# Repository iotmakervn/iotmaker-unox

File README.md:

# IoT Maker - UnoX

## Features

IoTMaker UnoX:  
- Power input 6.5V to 12VDC - recomment 9V (1A/5V output) and 5V USB
- Additional Button, LED, header for external module : variable, servo, common sensor.
- Open hardware with CC-BY-SA license
- Design with KiCad

## Hardware

### Schematics

### PCB Layout

### 3D

### Pinout 

### Gerber

[Download gerber sigle](./assets/iotmaker-arduino-uno-68,58x53,34mm.zip)

[Download gerber panel](./assets/panel-iotmaker-arduino-uno.zip)

### Remark

This project was in development phase - we will remove this remark after release

# License

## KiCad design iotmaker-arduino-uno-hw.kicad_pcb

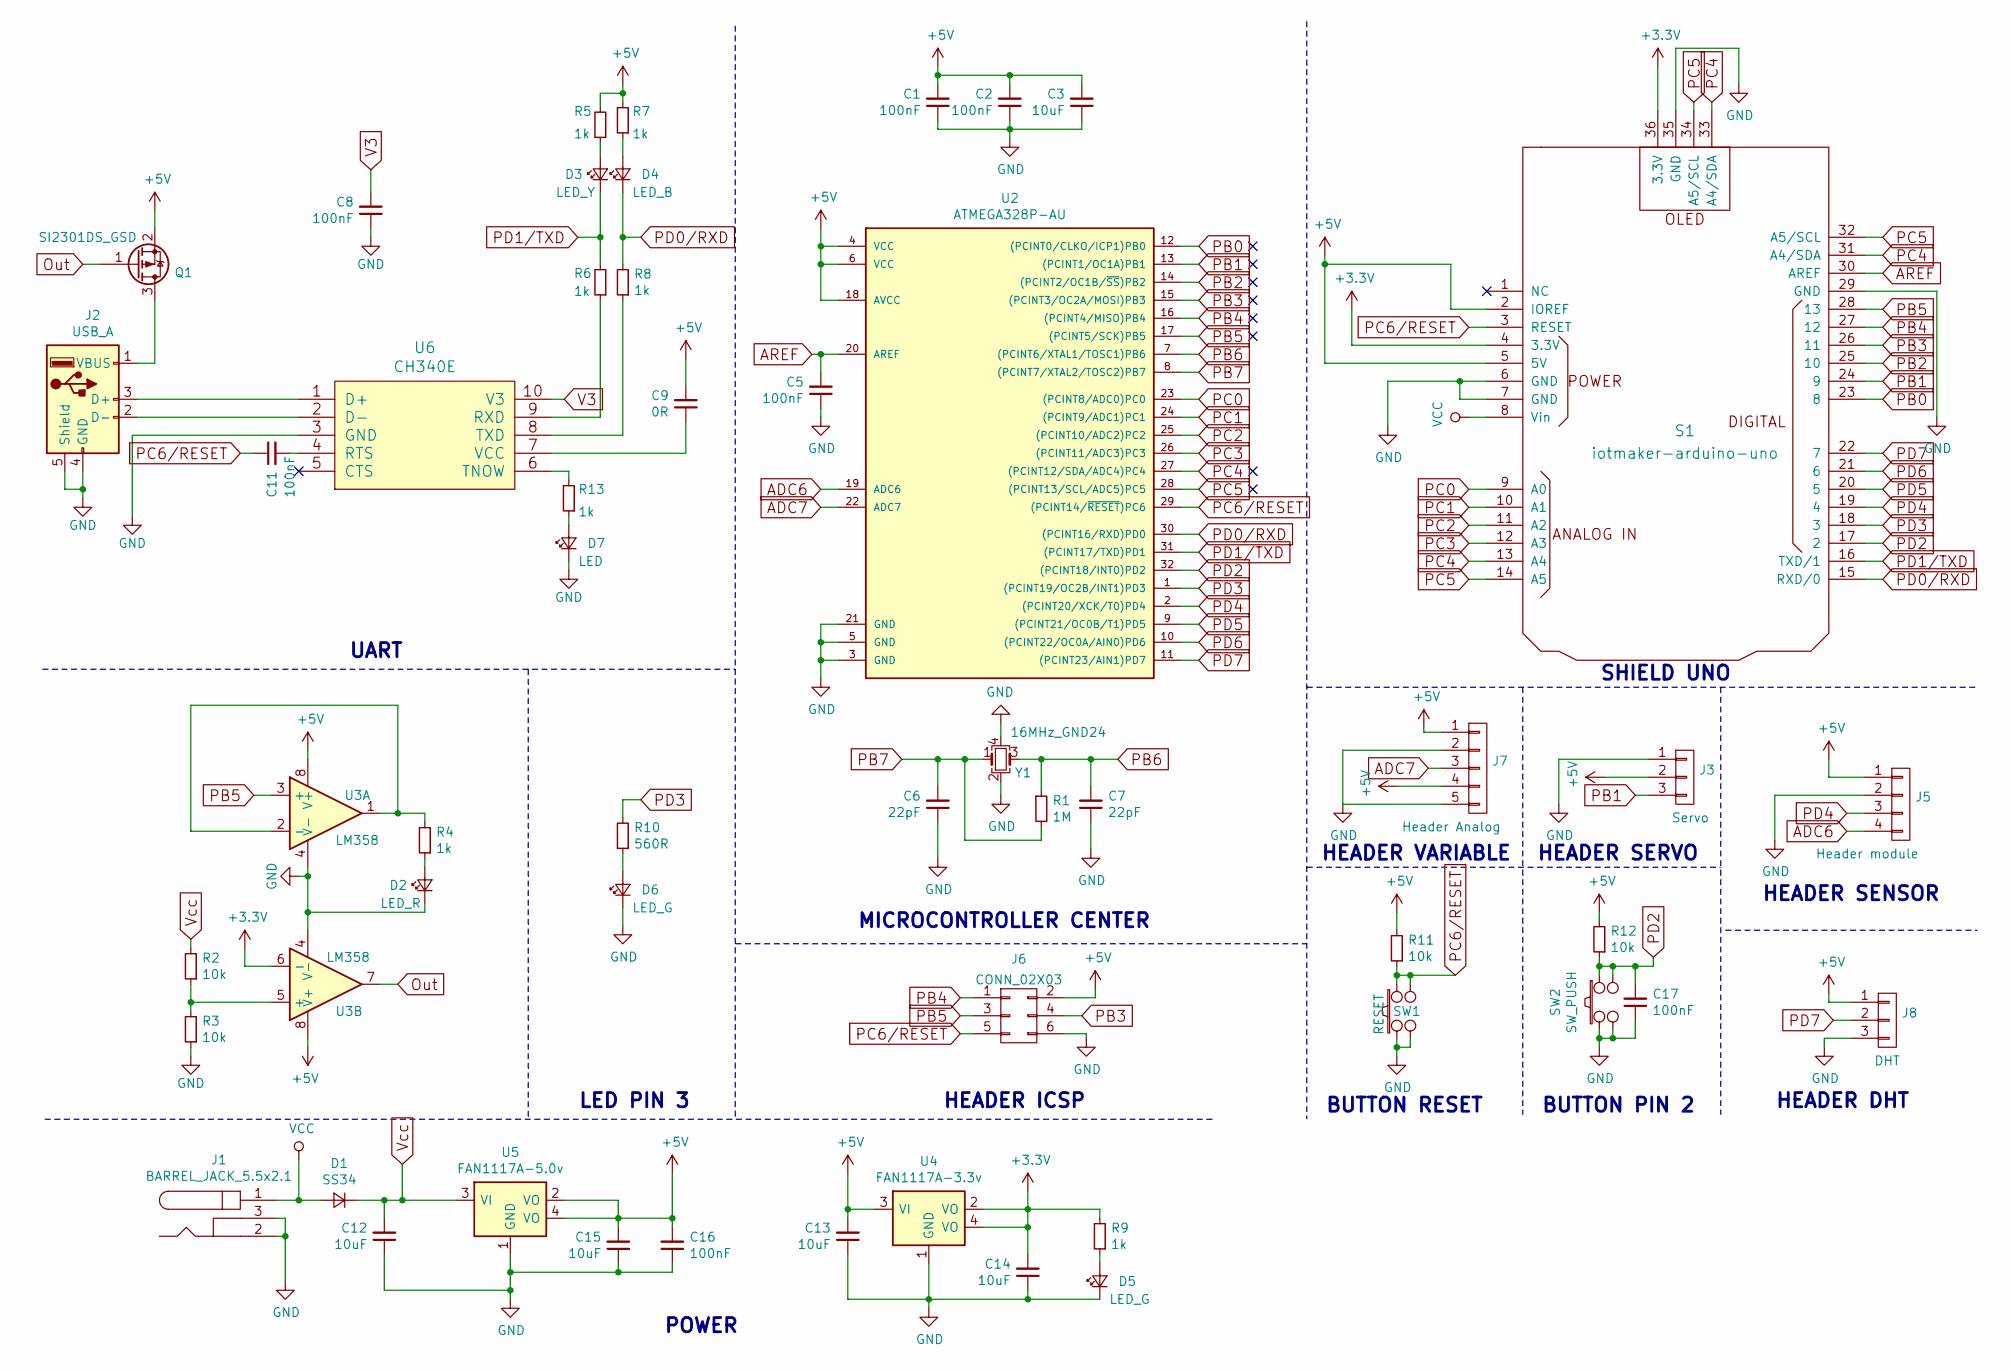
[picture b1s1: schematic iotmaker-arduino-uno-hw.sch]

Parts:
C1, C2, C5, C8, C11, C16, C17: 100nF; C_0603
C3: 10uF; C_0603
C6, C7: 22pF; C_0603
C9: 0R; C_0603
C12, C13, C14, C15: 10uF; C_1210
D1: SS34; D_SMA-SMB_Universal_Handsoldering
D2: LED_R; LED_0603
D3: LED_Y; LED_0603
D4: LED_B; LED_0603
D5, D6: LED_G; LED_0603
D7: LED; LED_0603
J1: BARREL_JACK_5.5x2.1; BARREL_JACK
J2: USB_A; MicroUSB-B
J3: Servo; Pin_Header_Straight_1x03_Pitch2.54mm
J5: Header module; Pin_Header_Straight_1x04_Pitch2.54mm
J6: CONN_02X03; Pin_Header_Straight_2x03_Pitch2.54mm
J7: Header Analog; Pin_Header_Straight_1x05_Pitch2.54mm
J8: DHT; Pin_Header_Straight_1x03_Pitch2.54mm
Q1: SI2301DS_GSD; SOT-23_standar
R1: 1M; R_0603
R2, R3, R11, R12: 10k; R_0603
R4, R5, R6, R7, R8, R9, R13: 1k; R_0603
R10: 560R; R_0603
S1: iotmaker-arduino-uno
SW1: RESET; smd_push2
SW2: SW_PUSH; smd_push2
U2: ATMEGA328P-AU; TQFP-32_7x7mm_Pitch0.8mm
U3: LM358; SOIC-8_3.9x4.9mm_Pitch1.27mm
U4: FAN1117A-3.3v; SOT-223
U5: FAN1117A-5.0v; SOT-223
U6: CH340E; MSOP-10_3x3mm_Pitch0.5mm
Y1: 16MHz_GND24; Crystal_SMD_3225-4pin_3.2x2.5mm

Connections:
+3V3: C14.2, R9.2, S1.4 (3.3V), S1.36 (3.3V), U3.6 (-), U4.2 (VO), U4.4 (VO)
+5V: C1.2, C2.2, C3.2, C9.2, C13.2, C15.2, C16.2, J3.2, J5.1, J6.2, J7.1, J7.4, J8.1, Q1.2 (S), R5.2, R7.2, R11.2, R12.2, S1.2 (IOREF), S1.5 (5V), U2.4 (VCC), U2.6 (VCC), U2.18 (AVCC), U3.8 (V+), U4.3 (VI), U5.2 (VO), U5.4 (VO)
ADC6: J5.4, U2.19 (ADC6)
ADC7: J7.3, U2.22 (ADC7)
AREF: C5.2, S1.30 (AREF), U2.20 (AREF)
GND: C1.1, C2.1, C3.1, C5.1, C6.1, C7.1, C8.1, C12.1, C13.1, C14.1, C15.1, C16.1, C17.1, D2.1 (K), D5.1 (K), D6.1 (K), D7.1 (K), J1.2, J1.3, J2.4 (GND), J2.5 (Shield), J3.1, J5.2, J6.6, J7.2, J7.5, J8.3, R3.1, S1.6 (GND), S1.7 (GND), S1.29 (GND), S1.35 (GND), SW1.1, SW1.2, SW2.3, SW2.4, U2.3 (GND), U2.5 (GND), U2.21 (GND), U3.4 (V-), U4.1 (GND), U5.1 (GND), U6.3 (GND), Y1.2, Y1.4
unnamed: C9.1, U6.7 (VCC)
unnamed: C11.2, U6.4 (RTS)
unnamed: D2.2 (A), R4.1
unnamed: D3.2 (A), R5.1
unnamed: D4.2 (A), R7.1
unnamed: D5.2 (A), R9.1
unnamed: D6.2 (A), R10.1
unnamed: D7.2 (A), R13.1
unnamed: J2.1 (VBUS), Q1.3 (D)
unnamed: J2.2 (D-), U6.2 (D-)
unnamed: J2.3 (D+), U6.1 (D+)
unnamed: R2.1, R3.2, U3.5 (+)
unnamed: R4.2, U3.1, U3.2 (-)
unnamed: R6.1, U6.9 (RXD)
unnamed: R8.1, U6.8 (TXD)
unnamed: R13.2, U6.6 (TNOW)
Out: Q1.1 (G), U3.7
PB0: S1.23 (8), U2.12 ((PCINT0/CLKO/ICP1)PB0)
PB1: J3.3, S1.24 (9), U2.13 ((PCINT1/OC1A)PB1)
PB2: S1.25 (10), U2.14 ((PCINT2/OC1B/~SS~)PB2)
PB3: J6.4, S1.26 (11), U2.15 ((PCINT3/OC2A/MOSI)PB3)
PB4: J6.1, S1.27 (12), U2.16 ((PCINT4/MISO)PB4)
PB5: J6.3, S1.28 (13), U2.17 ((PCINT5/SCK)PB5), U3.3 (+)
PB6: C7.2, R1.1, U2.7 ((PCINT6/XTAL1/TOSC1)PB6), Y1.3
PB7: C6.2, R1.2, U2.8 ((PCINT7/XTAL2/TOSC2)PB7), Y1.1
PC0: S1.9 (A0), U2.23 ((PCINT8/ADC0)PC0)
PC1: S1.10 (A1), U2.24 ((PCINT9/ADC1)PC1)
PC2: S1.11 (A2), U2.25 ((PCINT10/ADC2)PC2)
PC3: S1.12 (A3), U2.26 ((PCINT11/ADC3)PC3)
PC4: S1.13 (A4), S1.31 (A4/SDA), S1.33 (A4/SDA), U2.27 ((PCINT12/SDA/ADC4)PC4)
PC5: S1.14 (A5), S1.32 (A5/SCL), S1.34 (A5/SCL), U2.28 ((PCINT13/SCL/ADC5)PC5)
PC6/RESET: C11.1, J6.5, R11.1, S1.3 (RESET), SW1.3, SW1.4, U2.29 ((PCINT14/~RESET~)PC6)
PD0/RXD: D4.1 (K), R8.2, S1.15 (RXD/0), U2.30 ((PCINT16/RXD)PD0)
PD1/TXD: D3.1 (K), R6.2, S1.16 (TXD/1), U2.31 ((PCINT17/TXD)PD1)
PD2: C17.2, R12.1, S1.17 (2), SW2.1, SW2.2, U2.32 ((PCINT18/INT0)PD2)
PD3: R10.2, S1.18 (3), U2.1 ((PCINT19/OC2B/INT1)PD3)
PD4: J5.3, S1.19 (4), U2.2 ((PCINT20/XCK/T0)PD4)
PD5: S1.20 (5), U2.9 ((PCINT21/OC0B/T1)PD5)
PD6: S1.21 (6), U2.10 ((PCINT22/OC0A/AIN0)PD6)
PD7: J8.2, S1.22 (7), U2.11 ((PCINT23/AIN1)PD7)
V3: C8.2, U6.10 (V3)
VCC: D1.2 (A), J1.1, S1.8 (Vin)
Vcc: C12.2, D1.1 (K), R2.2, U5.3 (VI)

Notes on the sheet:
BUTTON RESET
BUTTON PIN 2
HEADER DHT
HEADER SENSOR
HEADER SERVO
HEADER VARIABLE
SHIELD UNO
HEADER ICSP
MICROCONTROLLER CENTER
LED PIN 3
UART
POWER

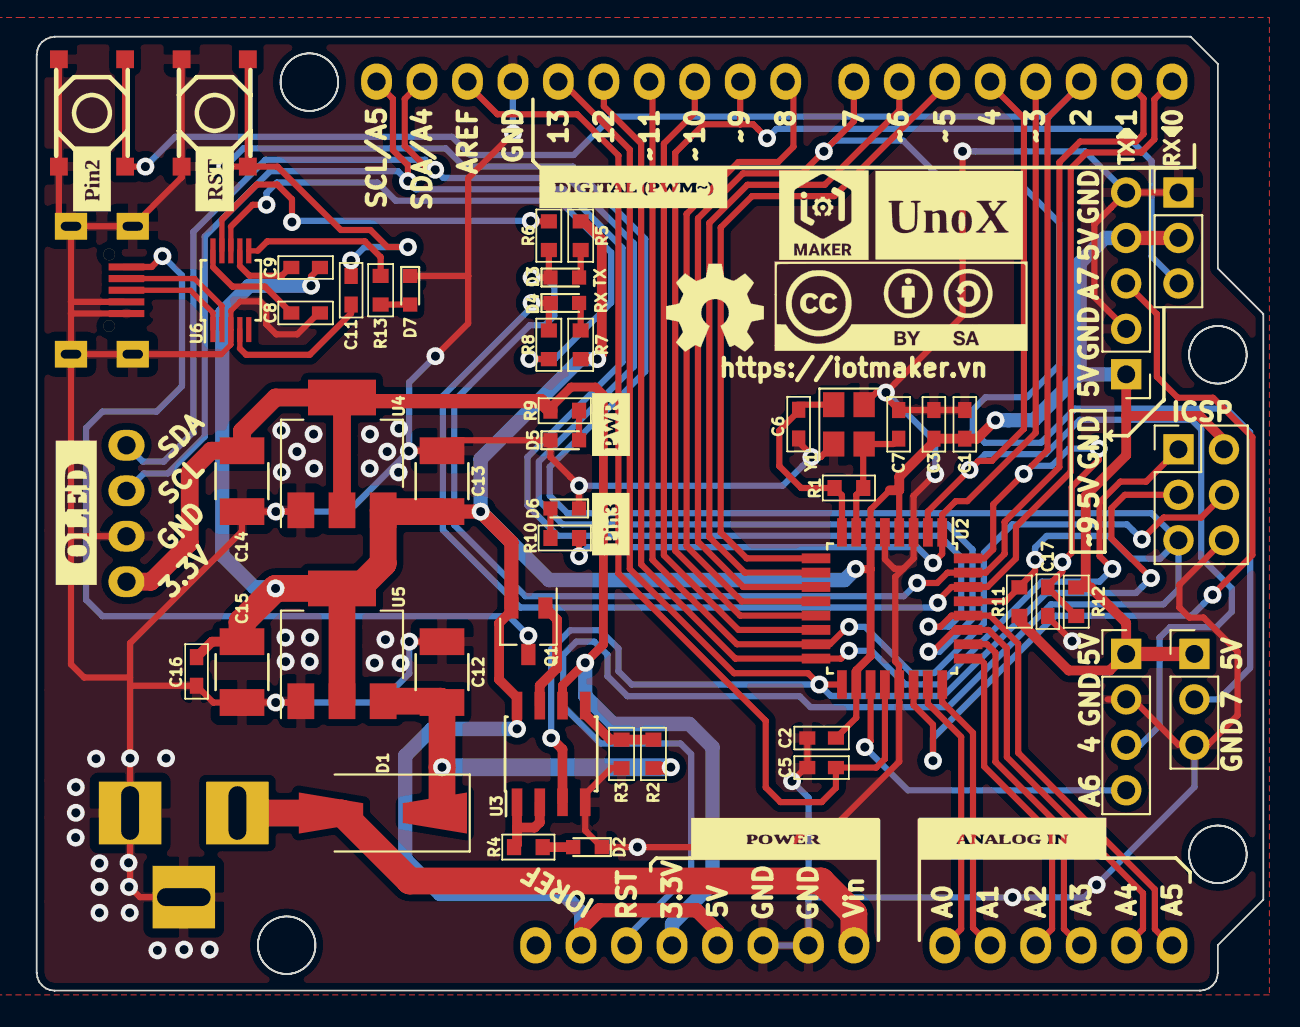
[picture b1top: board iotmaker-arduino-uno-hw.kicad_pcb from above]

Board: 2 copper layers, 68.5 x 53.3 mm, 52 parts (0 on the bottom side), 49 nets.

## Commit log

2018-01-02 Final basic schematic & pcb
2018-01-06 basic completed pcb
2018-01-06 cchange CH340G to CH340E & update information board, gerber file
2018-01-30 drop c4
2018-01-30 remap symbol with new version kicad
2018-01-30 change button pin8 to pin2 and header pin2 to pin7
2018-01-30 final modify board and update assets
2018-02-02 add gerber 4 panel
2018-02-02 add link download gerber 4 panel
2018-02-02 rename link download
2018-02-05 update gerber pcb & gerber 4 panel
2018-02-05 update picture

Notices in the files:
README.md:
License:
http://mirrors.creativecommons.org/presskit/buttons/88x31/png/by-sa.png
